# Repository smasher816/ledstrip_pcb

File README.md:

# Ledstrip PCB

Kicad files for my ledstrip project.

# Top

# Bottom

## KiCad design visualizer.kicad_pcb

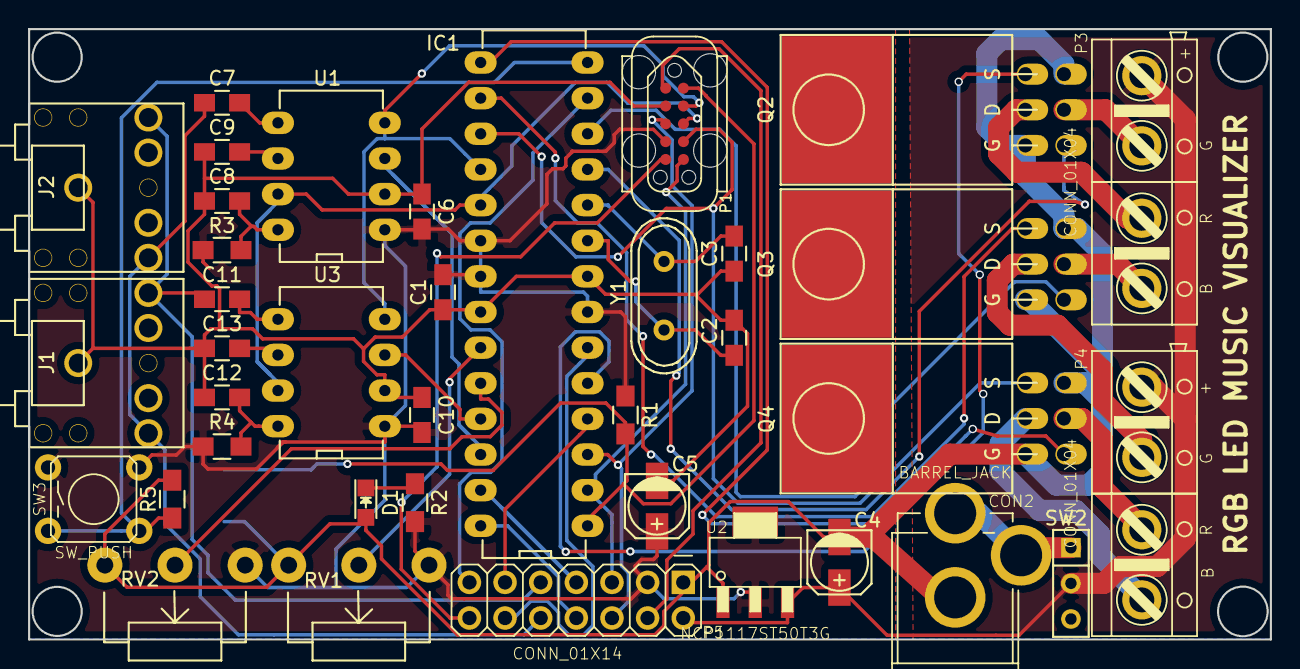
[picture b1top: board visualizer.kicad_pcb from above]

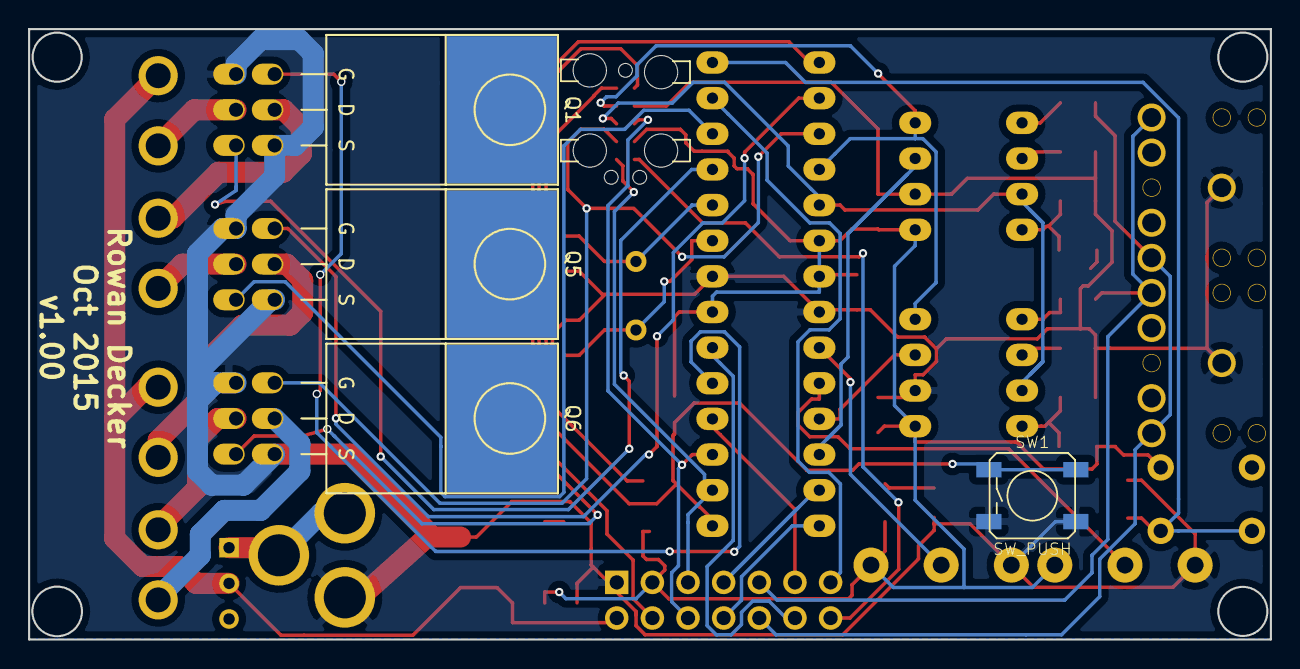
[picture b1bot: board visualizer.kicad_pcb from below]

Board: 2 copper layers, 88.5 x 43.5 mm, 42 parts (4 on the bottom side), 44 nets.

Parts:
C1, C6, C9, C10, C13: 100nF; C_0805_HandSoldering
C2, C3: 22pF; C_0805_HandSoldering
C4, C5: 10uF; c_elec_4x4.5
C7, C11: 10nF; C_0805_HandSoldering
C8, C12: 33pF; C_0805_HandSoldering
CON2: BARREL_JACK; AB2_PB_2MM_JACK_PTH
D1: PWRLED; LED-0805
IC1: ATMEGA328P; DIP-28
J1, J2: AUDIO-JACK; AUDIO_JACK-3.5mm
P1: TC2050-IDC; TC2050_BIG
P3, P4: CONN_01X04; AB2_TB_04_RA_5MM_L-BLK
P5: CONN_01X14; AB2_HDR_M07-2V
Q1, Q2, Q3, Q4, Q5, Q6: N-MOSFET; TO-220_NFET_Horizontal
R1, R5: 10K; R_0805_HandSoldering
R2: R; R_0805_HandSoldering
R3, R4: 200K; R_0805_HandSoldering
RV1, RV2: POT; Potentiometer_WirePads
SW1: SW_PUSH; AB2_PB_MOM_5.2MM_SMD
SW2: SPST; SW_Micro_SPST
SW3: SW_PUSH; AB2_PB_MOM_6MM_PTH_BLK
U1, U3: MSGEQ7; DIP-8
U2: NCP1117ST50T3G; AB2_SOT223
Y1: 16Mhz; Crystal_HC49-U_Vertical

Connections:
+3V3: P1.1, P5.4
+5V: C1.1, C5.1, C6.1, C10.1, IC1.7, IC1.20, IC1.21, P1.4, P5.3, R1.2, R2.2, R3.2, R4.2, RV1.1, RV2.1, SW3.1, U1.1, U2.2, U3.1
+12V: C4.1, P3.1, P4.1, P5.2, SW2.2, U2.3
/AUX: P1.5, P5.14
/B1: IC1.12, Q3.G
/B2: IC1.17, P1.7, Q6.G
/BTN1: IC1.14, R5.2, SW3.2
/CLK: IC1.19, P1.8, U1.7, U3.7
/D2: IC1.4, P5.11
/D4: IC1.6, P5.12
/D7: IC1.13, P5.13
/EQ1: IC1.25, U3.3
/EQ2: IC1.26, U1.3
/G1: IC1.11, Q2.G
/G2: IC1.16, Q5.G
/LED_B1: P3.4, Q3.D
/LED_B2: P4.4, Q6.D
/LED_G1: P3.2, Q2.D
/LED_G2: P4.2, Q5.D
/LED_R1: P3.3, Q1.D
/LED_R2: P4.3, Q4.D
/LEFT: C11.2, J1.2, J2.2, P5.9
/MISO: IC1.18, P1.9, U1.4, U3.4
/POT1: IC1.23, RV1.2
/POT2: IC1.24, RV2.2
/PWR_IN: CON2.1, CON2.3, SW2.1
/R1: IC1.5, Q1.G
/R2: IC1.15, Q4.G
/RESET: IC1.1, P1.10, R1.1, SW1.1
/RIGHT: C7.2, J1.3, J2.3, P5.10
/RX: IC1.2, P1.6, P5.5
/SCL: IC1.28, P5.8
/SDA: IC1.27, P5.7
/TX: IC1.3, P1.3, P5.6
/XTAL1: C3.1, IC1.10, Y1.1
/XTAL2: C2.2, IC1.9, Y1.2
GND: C1.2, C2.1, C3.2, C4.2, C5.2, C6.2, C8.1, C9.2, C10.2, C12.1, C13.2, CON2.2, D1.2, IC1.8, IC1.22, J1.1, J2.1, P1.2, P5.1, Q1.S, Q2.S, Q3.S, Q4.S, Q5.S, Q6.S, R5.1, RV1.3, RV2.3, SW1.2, U1.2, U2.1, U3.2
unnamed: C7.1, U1.5
unnamed: C8.2, R3.1, U1.8
unnamed: C9.1, U1.6
unnamed: C11.1, U3.5
unnamed: C12.2, R4.1, U3.8
unnamed: C13.1, U3.6
unnamed: D1.1, R2.1

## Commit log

2016-05-03 Add V1
2016-05-03 Add README
